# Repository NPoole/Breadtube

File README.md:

# BREADTOOB
[![CC BY-SA 4.0][cc-by-sa-shield]][cc-by-sa]

Noval/Heptal Miniature Tube Socket Breadboard

[cc-by-sa]: http://creativecommons.org/licenses/by-sa/4.0/
[cc-by-sa-shield]: https://img.shields.io/badge/License-CC%20BY--SA%204.0-lightgrey.svg

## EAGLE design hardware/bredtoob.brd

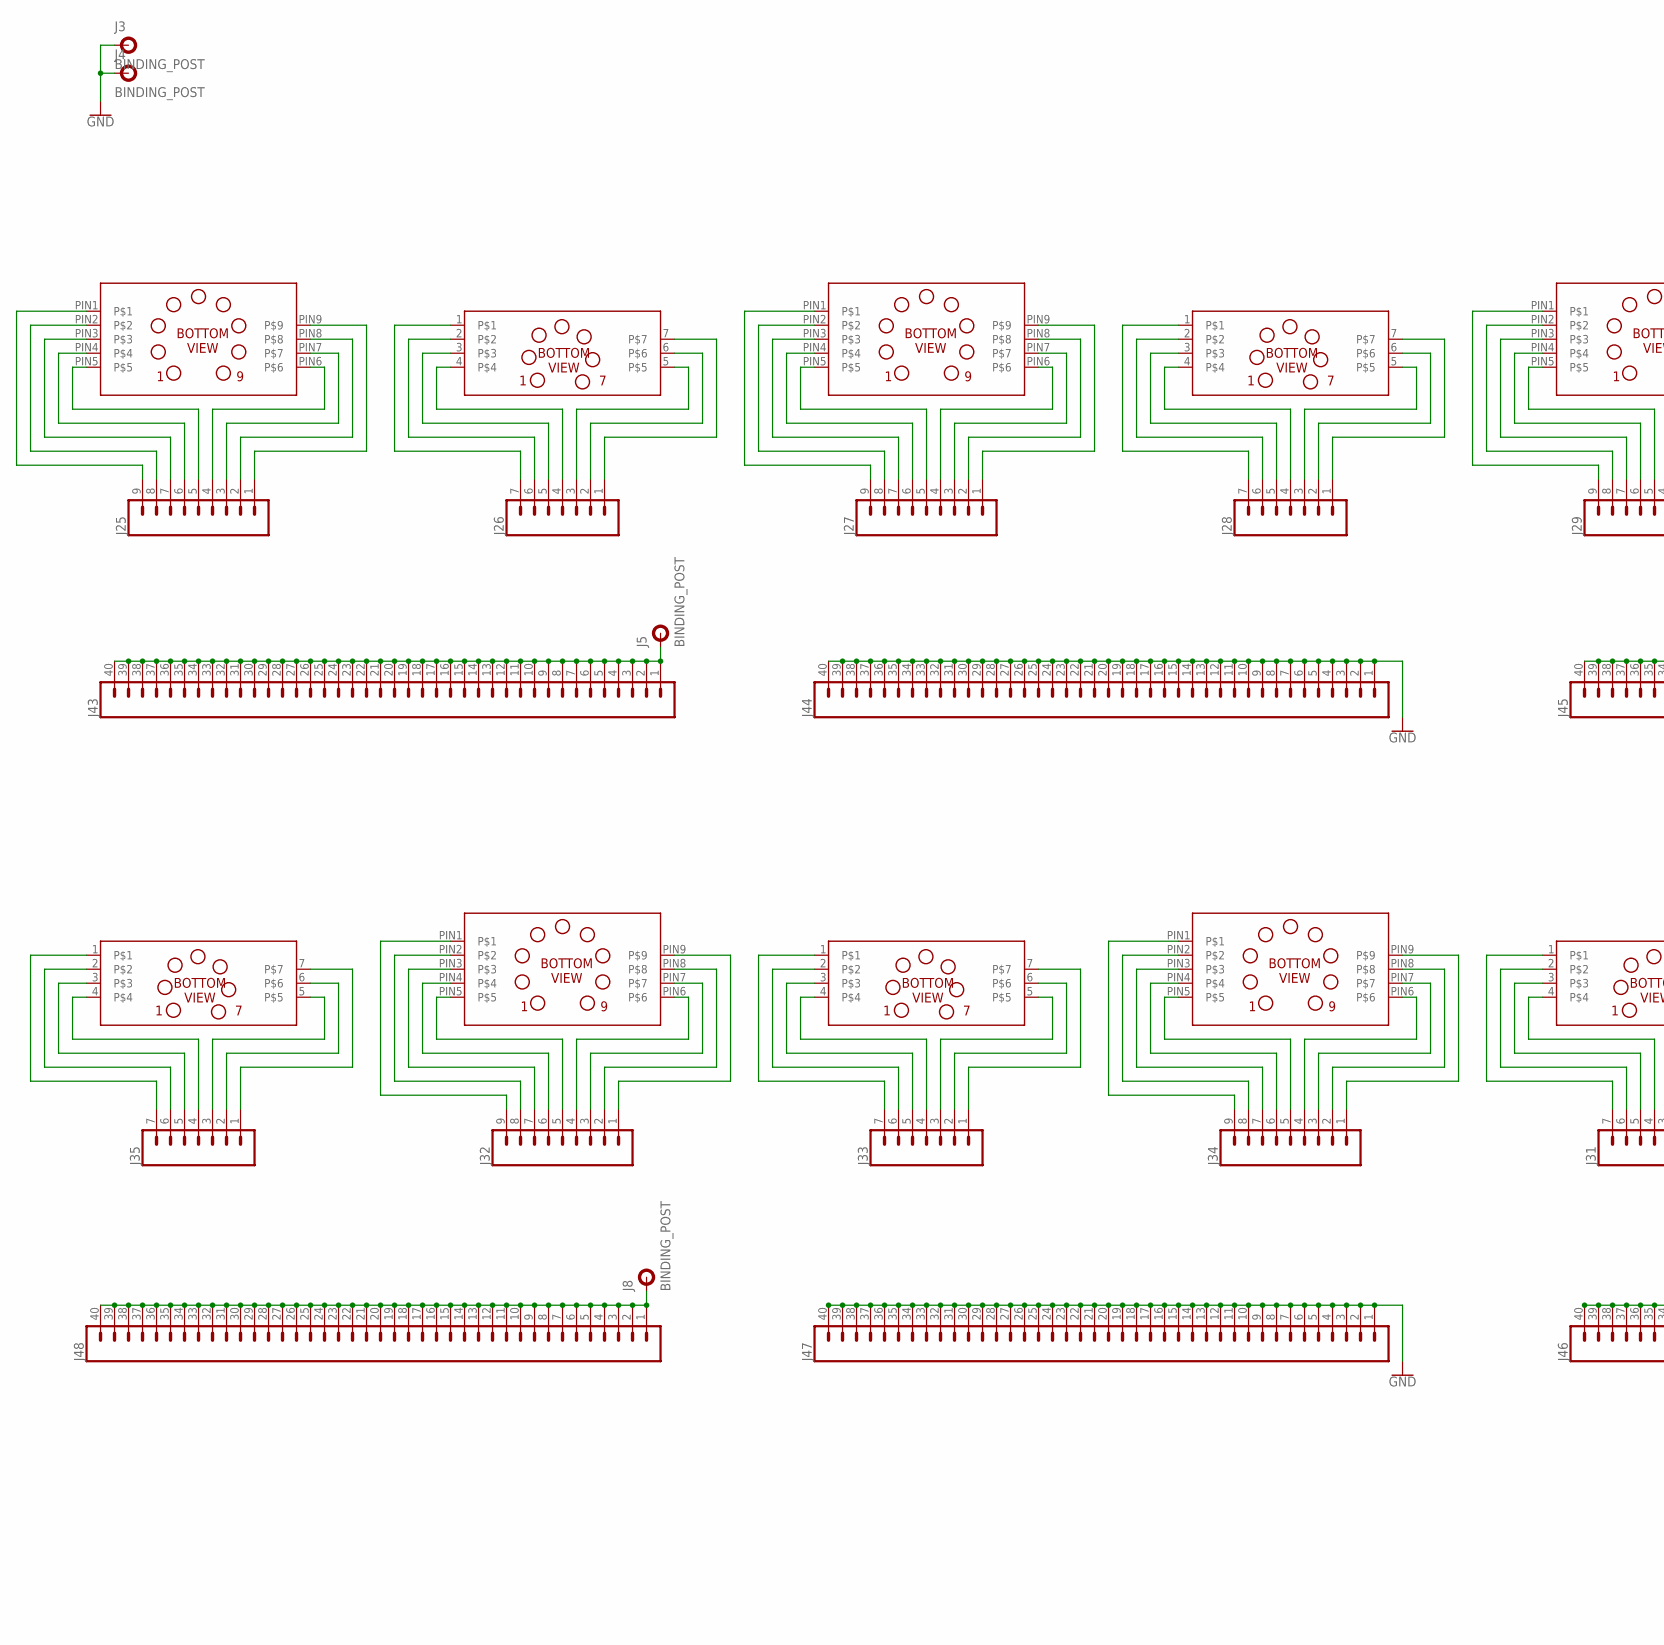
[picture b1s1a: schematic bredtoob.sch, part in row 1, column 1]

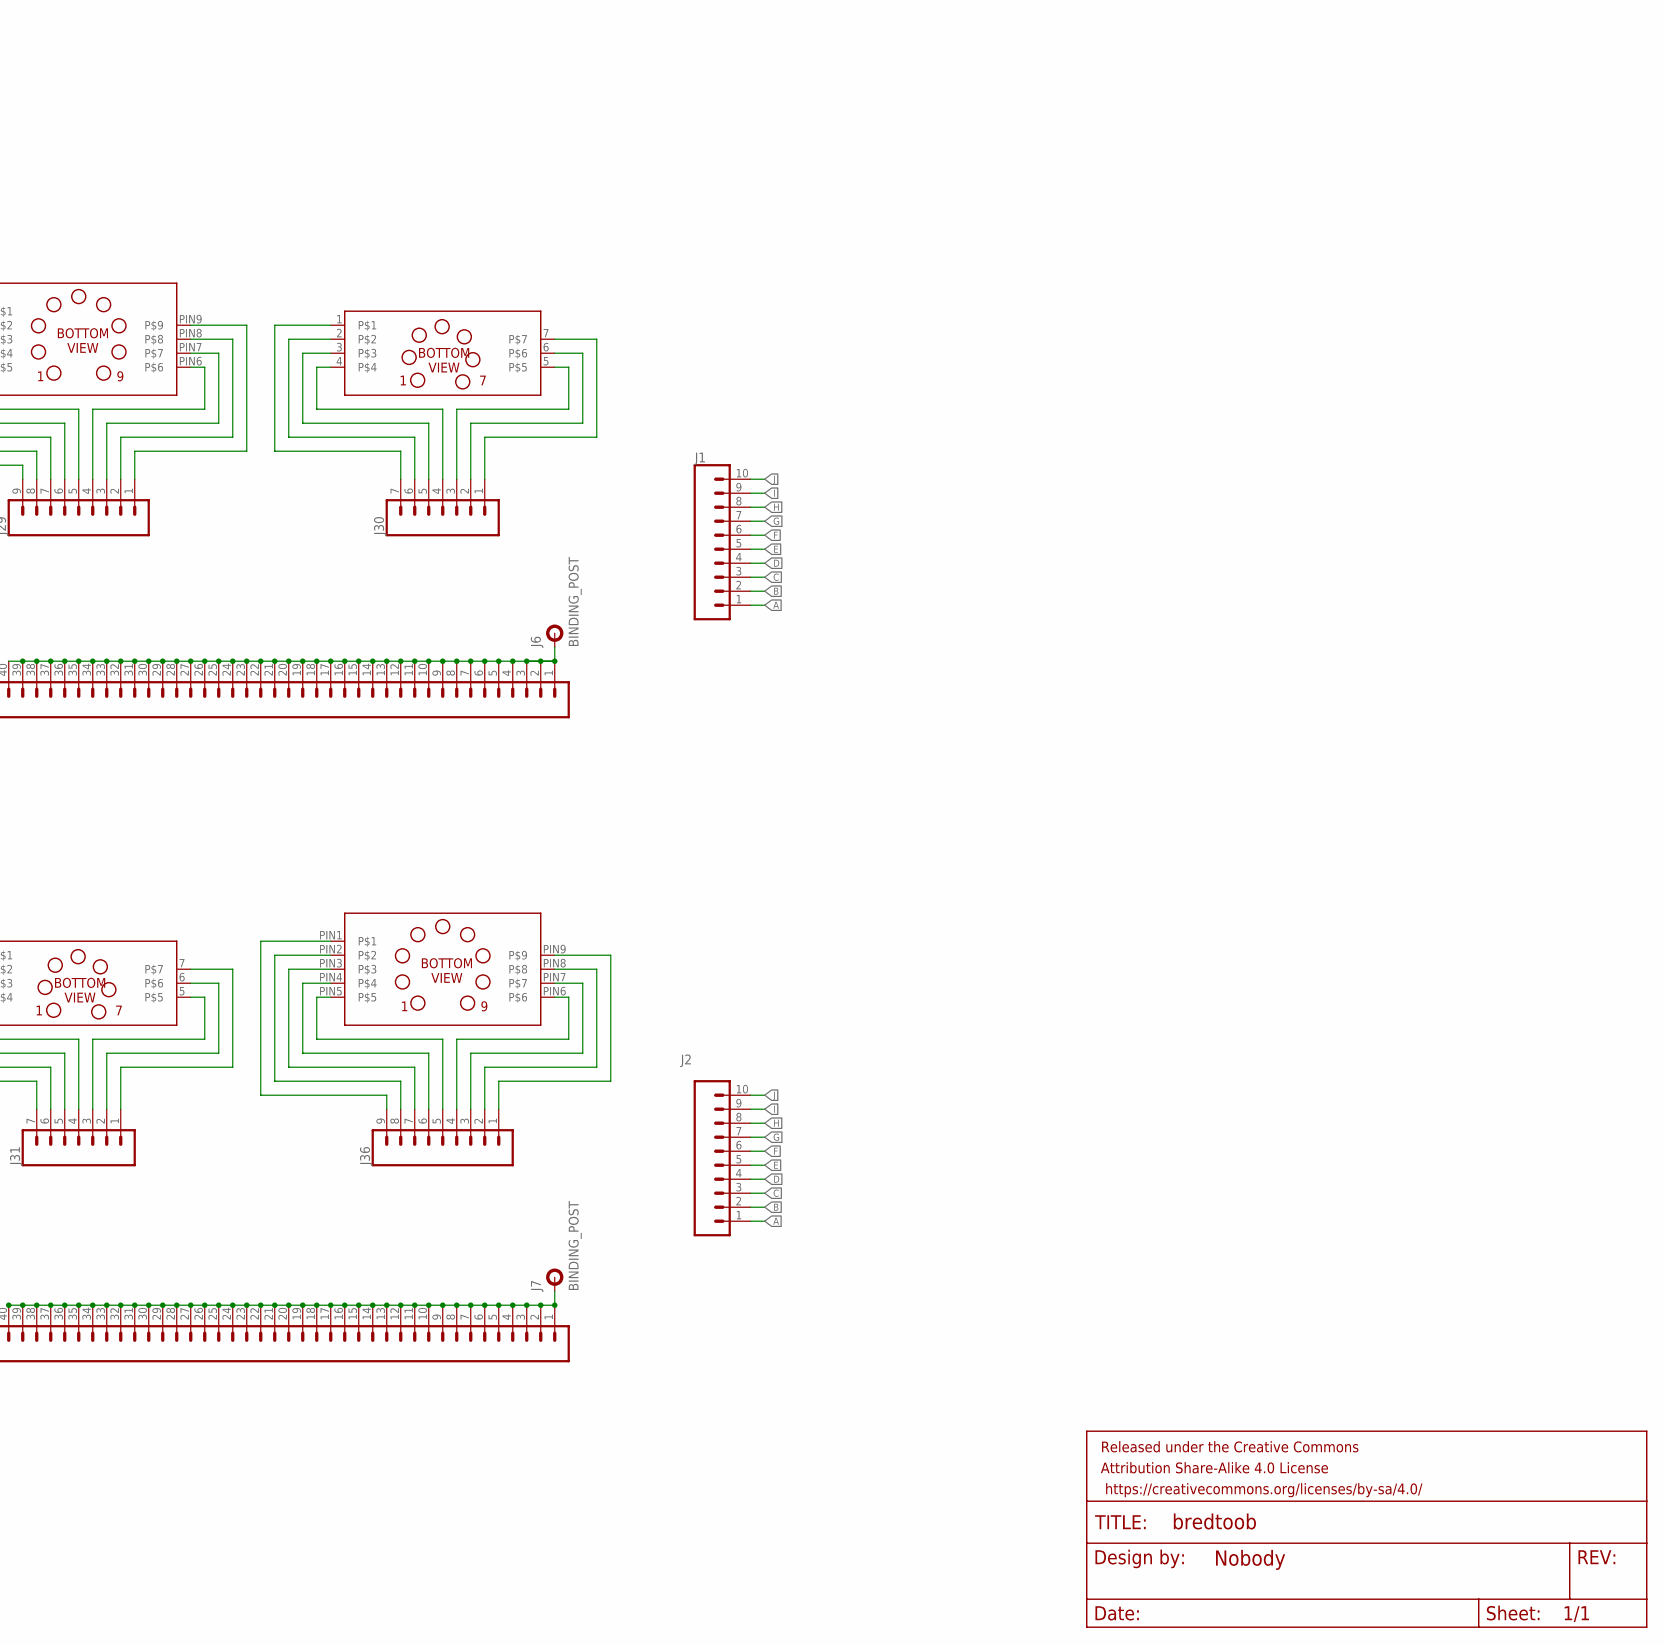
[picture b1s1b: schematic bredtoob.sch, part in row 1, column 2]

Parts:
FRAME1: FRAME-LETTERNO_PACKAGE; DUMMY
J1, J2: CONN_10NO_SILK_PTH_FEMALE; 1X10_NO_SILK
J3, J4, J5, J6, J7, J8: BINDING_POST
J25, J27, J29, J32, J34, J36: CONN_09; 1X09
J26, J28, J30, J31, J33, J35: CONN_07NO_SILK; 1X07_NO_SILK
J43, J44, J45, J46, J47, J48: CONN_40; 1X40
U$1, U$3, U$5, U$8, U$10, U$12: 9PINMINI; 9-PIN-MINIATURE
U$2, U$4, U$6, U$7, U$9, U$11: 7PINMINI; 7-PIN-MINIATURE(B7G)

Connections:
A: J1.1, J2.1
B: J1.2, J2.2
C: J1.3, J2.3
D: J1.4, J2.4
E: J1.5, J2.5
F: J1.6, J2.6
G: J1.7, J2.7
GND: J3.P$1, J4.P$1, J44.1, J44.2, J44.3, J44.4, J44.5, J44.6, J44.7, J44.8, J44.9, J44.10, J44.11, J44.12, J44.13, J44.14, J44.15, J44.16, J44.17, J44.18, J44.19, J44.20, J44.21, J44.22, J44.23, J44.24, J44.25, J44.26, J44.27, J44.28, J44.29, J44.30, J44.31, J44.32, J44.33, J44.34, J44.35, J44.36, J44.37, J44.38, J44.39, J44.40, J47.1, J47.2, J47.3, J47.4, J47.5, J47.6, J47.7, J47.8, J47.9, J47.10, J47.11, J47.12, J47.13, J47.14, J47.15, J47.16, J47.17, J47.18, J47.19, J47.20, J47.21, J47.22, J47.23, J47.24, J47.25, J47.26, J47.27, J47.28, J47.29, J47.30, J47.31, J47.32, J47.33, J47.34, J47.35, J47.36, J47.37, J47.38, J47.39, J47.40
H: J1.8, J2.8
I: J1.9, J2.9
J: J1.10, J2.10
unnamed: J5.P$1, J43.1, J43.2, J43.3, J43.4, J43.5, J43.6, J43.7, J43.8, J43.9, J43.10, J43.11, J43.12, J43.13, J43.14, J43.15, J43.16, J43.17, J43.18, J43.19, J43.20, J43.21, J43.22, J43.23, J43.24, J43.25, J43.26, J43.27, J43.28, J43.29, J43.30, J43.31, J43.32, J43.33, J43.34, J43.35, J43.36, J43.37, J43.38, J43.39, J43.40
unnamed: J6.P$1, J45.1, J45.2, J45.3, J45.4, J45.5, J45.6, J45.7, J45.8, J45.9, J45.10, J45.11, J45.12, J45.13, J45.14, J45.15, J45.16, J45.17, J45.18, J45.19, J45.20, J45.21, J45.22, J45.23, J45.24, J45.25, J45.26, J45.27, J45.28, J45.29, J45.30, J45.31, J45.32, J45.33, J45.34, J45.35, J45.36, J45.37, J45.38, J45.39, J45.40
unnamed: J7.P$1, J46.1, J46.2, J46.3, J46.4, J46.5, J46.6, J46.7, J46.8, J46.9, J46.10, J46.11, J46.12, J46.13, J46.14, J46.15, J46.16, J46.17, J46.18, J46.19, J46.20, J46.21, J46.22, J46.23, J46.24, J46.25, J46.26, J46.27, J46.28, J46.29, J46.30, J46.31, J46.32, J46.33, J46.34, J46.35, J46.36, J46.37, J46.38, J46.39, J46.40
unnamed: J8.P$1, J48.1, J48.2, J48.3, J48.4, J48.5, J48.6, J48.7, J48.8, J48.9, J48.10, J48.11, J48.12, J48.13, J48.14, J48.15, J48.16, J48.17, J48.18, J48.19, J48.20, J48.21, J48.22, J48.23, J48.24, J48.25, J48.26, J48.27, J48.28, J48.29, J48.30, J48.31, J48.32, J48.33, J48.34, J48.35, J48.36, J48.37, J48.38, J48.39, J48.40
unnamed: J25.9, U$1.PIN1
unnamed: J25.8, U$1.PIN2
unnamed: J25.7, U$1.PIN3
unnamed: J25.6, U$1.PIN4
unnamed: J25.5, U$1.PIN5
unnamed: J25.4, U$1.PIN6
unnamed: J25.3, U$1.PIN7
unnamed: J25.2, U$1.PIN8
unnamed: J25.1, U$1.PIN9
unnamed: J26.7, U$2.1
unnamed: J26.6, U$2.2
unnamed: J26.5, U$2.3
unnamed: J26.4, U$2.4
unnamed: J26.3, U$2.5
unnamed: J26.2, U$2.6
unnamed: J26.1, U$2.7
unnamed: J27.9, U$3.PIN1
unnamed: J27.8, U$3.PIN2
unnamed: J27.7, U$3.PIN3
unnamed: J27.6, U$3.PIN4
unnamed: J27.5, U$3.PIN5
unnamed: J27.4, U$3.PIN6
unnamed: J27.3, U$3.PIN7
unnamed: J27.2, U$3.PIN8
unnamed: J27.1, U$3.PIN9
unnamed: J28.7, U$4.1
unnamed: J28.6, U$4.2
unnamed: J28.5, U$4.3
unnamed: J28.4, U$4.4
unnamed: J28.3, U$4.5
unnamed: J28.2, U$4.6
unnamed: J28.1, U$4.7
unnamed: J29.9, U$5.PIN1
unnamed: J29.8, U$5.PIN2
unnamed: J29.7, U$5.PIN3
unnamed: J29.6, U$5.PIN4
unnamed: J29.5, U$5.PIN5
unnamed: J29.4, U$5.PIN6
unnamed: J29.3, U$5.PIN7
unnamed: J29.2, U$5.PIN8
unnamed: J29.1, U$5.PIN9
unnamed: J30.7, U$6.1
unnamed: J30.6, U$6.2
unnamed: J30.5, U$6.3
unnamed: J30.4, U$6.4
unnamed: J30.3, U$6.5
unnamed: J30.2, U$6.6
unnamed: J30.1, U$6.7
unnamed: J35.7, U$7.1
unnamed: J35.6, U$7.2
unnamed: J35.5, U$7.3
unnamed: J35.4, U$7.4
unnamed: J35.3, U$7.5
unnamed: J35.2, U$7.6
unnamed: J35.1, U$7.7
unnamed: J32.9, U$8.PIN1
unnamed: J32.8, U$8.PIN2
unnamed: J32.7, U$8.PIN3
unnamed: J32.6, U$8.PIN4
unnamed: J32.5, U$8.PIN5
unnamed: J32.4, U$8.PIN6
unnamed: J32.3, U$8.PIN7
unnamed: J32.2, U$8.PIN8
unnamed: J32.1, U$8.PIN9
unnamed: J33.7, U$9.1
unnamed: J33.6, U$9.2
unnamed: J33.5, U$9.3
unnamed: J33.4, U$9.4
unnamed: J33.3, U$9.5
unnamed: J33.2, U$9.6
unnamed: J33.1, U$9.7
unnamed: J34.9, U$10.PIN1
unnamed: J34.8, U$10.PIN2
unnamed: J34.7, U$10.PIN3
unnamed: J34.6, U$10.PIN4
unnamed: J34.5, U$10.PIN5
unnamed: J34.4, U$10.PIN6
unnamed: J34.3, U$10.PIN7
unnamed: J34.2, U$10.PIN8
unnamed: J34.1, U$10.PIN9
unnamed: J31.7, U$11.1
unnamed: J31.6, U$11.2
unnamed: J31.5, U$11.3
unnamed: J31.4, U$11.4
unnamed: J31.3, U$11.5
unnamed: J31.2, U$11.6
unnamed: J31.1, U$11.7
unnamed: J36.9, U$12.PIN1
unnamed: J36.8, U$12.PIN2
unnamed: J36.7, U$12.PIN3
unnamed: J36.6, U$12.PIN4
unnamed: J36.5, U$12.PIN5
unnamed: J36.4, U$12.PIN6
unnamed: J36.3, U$12.PIN7
unnamed: J36.2, U$12.PIN8
unnamed: J36.1, U$12.PIN9

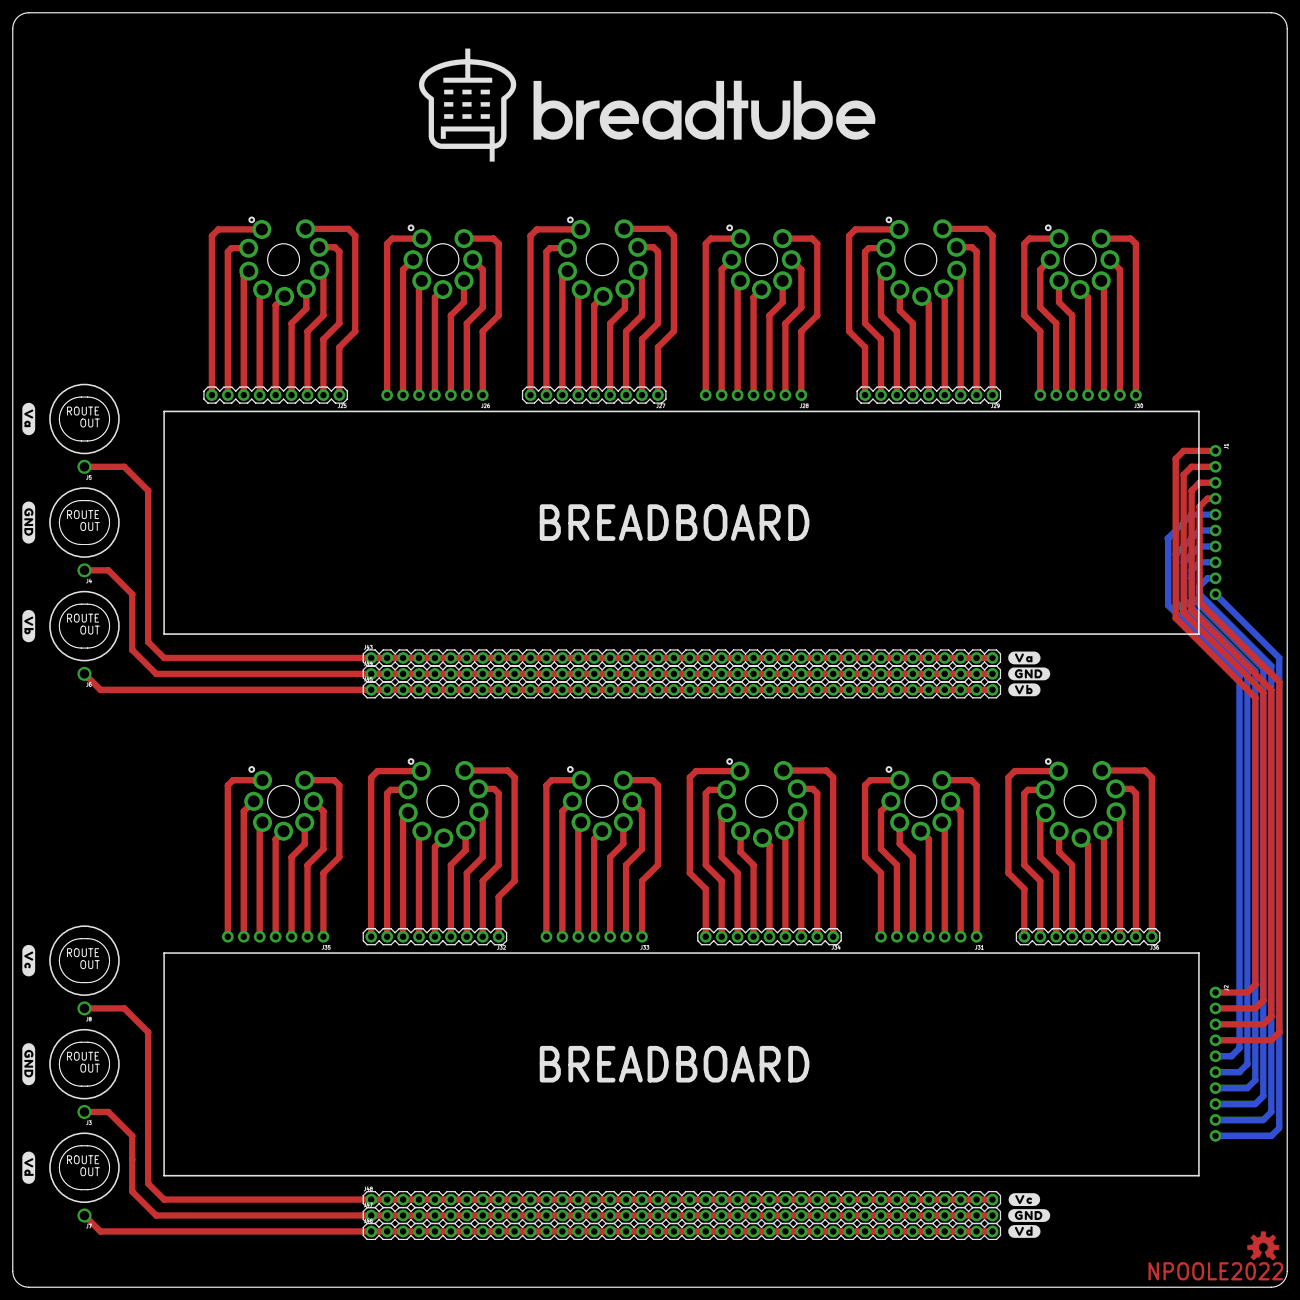
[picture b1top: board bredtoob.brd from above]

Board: 2 copper layers, 203.2 x 203.2 mm, 54 parts (0 on the bottom side), 111 nets.

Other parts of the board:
FRAME2: FRAME-LETTERNO_PACKAGE; DUMMY
U$13: LOGO#SVG0
U$14, U$15, U$20, U$21: #GND#0
U$16, U$22: #VA#0
U$17, U$23: #VB#0
U$18, U$24: #VC#0
U$19, U$25: #VD#0
U$26: OSHW-LOGO-M_COPPER

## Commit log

2022-04-07 housekeeping
2022-04-16 v02
    Swap half the noval tube sockets for b7g sockets so we support almost all miniature tubes (compactrons notwithstanding)
    Radius the corners of the board
    Reduce rails to 40 pins to match common header strips
    Add bus headers beside each breadboard to reduce mess if you need to wire between the two
2022-04-16 v03
    Glad I waited for parts to come in for testing before ordering v02
    - Replace banana jack headers with binding posts
    - Widen Pin Receptacle headers to accept Mill-Max 0312-0-15-80-34-80-10-0
    - Revise Silkscreen Labels
    - Add OSHW Logo
2022-04-16 Create LICENSE

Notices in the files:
parts and their libraries:
SparkFun-Aesthetics: Licensing: Creative Commons ShareAlike 4.0 International - https://creativecommons.org/licenses/by-sa/4.0
SparkFun-Aesthetics: Released under the Creative Commons Attribution Share-Alike 4.0 License
SparkFun-Aesthetics: https://creativecommons.org/licenses/by-sa/4.0
